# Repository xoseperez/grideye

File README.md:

# GridEye Camera

This is a 8x8 pixels IR camera based on the **Panasonic AMG88XX GridEye** sensors.
It uses a **WS2812 8x8 matrix** as camera display, an **128x32 uOLED display** for data and
a **Moteino** board with an ATMega328P microcontroller as controller.
It is powered by a **LiPo battery** connected to a **TP4056 based LiPO charger**.
There is also a **Pololu Adjustable Boost Regulator 2.5-9.5V** to power the LED matrix.

The AMG8833 is an 8x8 IR sensor by Panasonic with an I2C interface that reports concact-less temperature values from -20 to 80 celsius with a 2.5C accuracy and 0.25C resolution. It has a field view of ~60º and a max detection distance of 5 meters.

This is part of my "Slices" project, basically a sliced laser cut series of enclosures to house electronic projects.

## Hardware

### The electronics

The project relies on different discreet modules wired together. All the components (or compatible alternatives) are widely available. Only the AMG88XX board is custom made. Check the "amg8833" fordel in this repo for the Eagle files of the board.

All the dotted black lines in the drawing are connected together.

### The housing

The housing has been created using OpenSCAD and inspired by Pimoroni  PiBow enclosures for the RaspBerry Pi. I've been using this same technique lately on different project and I call them all under a common name: "Project Slices".

The enclosure is based on layers or "slices" of different materials.

* Transparent acrylic front-face
* Black cardboard mask
* White paper diffusor
* 4mm MDF grid that houses each LED in its own cubicle
* 2.5mm MDF cast for the LED matrix PCB
* 2.5mm MDF as support for the matrix PCB and uOLED board
* several (5) 4mm MDF hollow layers to house the electronics
* 2.5mm MDF as support for the AMG88XX board
* 4mm MDF hollow layers to house the AMG88XX board
* 2.5mm MDF as a back pane with a hole for the IR sensor

## Firmware

The project is ready to be build using [PlatformIO](http://www.platformio.org).
Please refer to their web page for instructions on how to install the builder.
Once installed:

```bash
> cd code
> platformio run
> platformio run --target upload
```

Library dependencies are automatically managed via PlatformIO Library Manager.

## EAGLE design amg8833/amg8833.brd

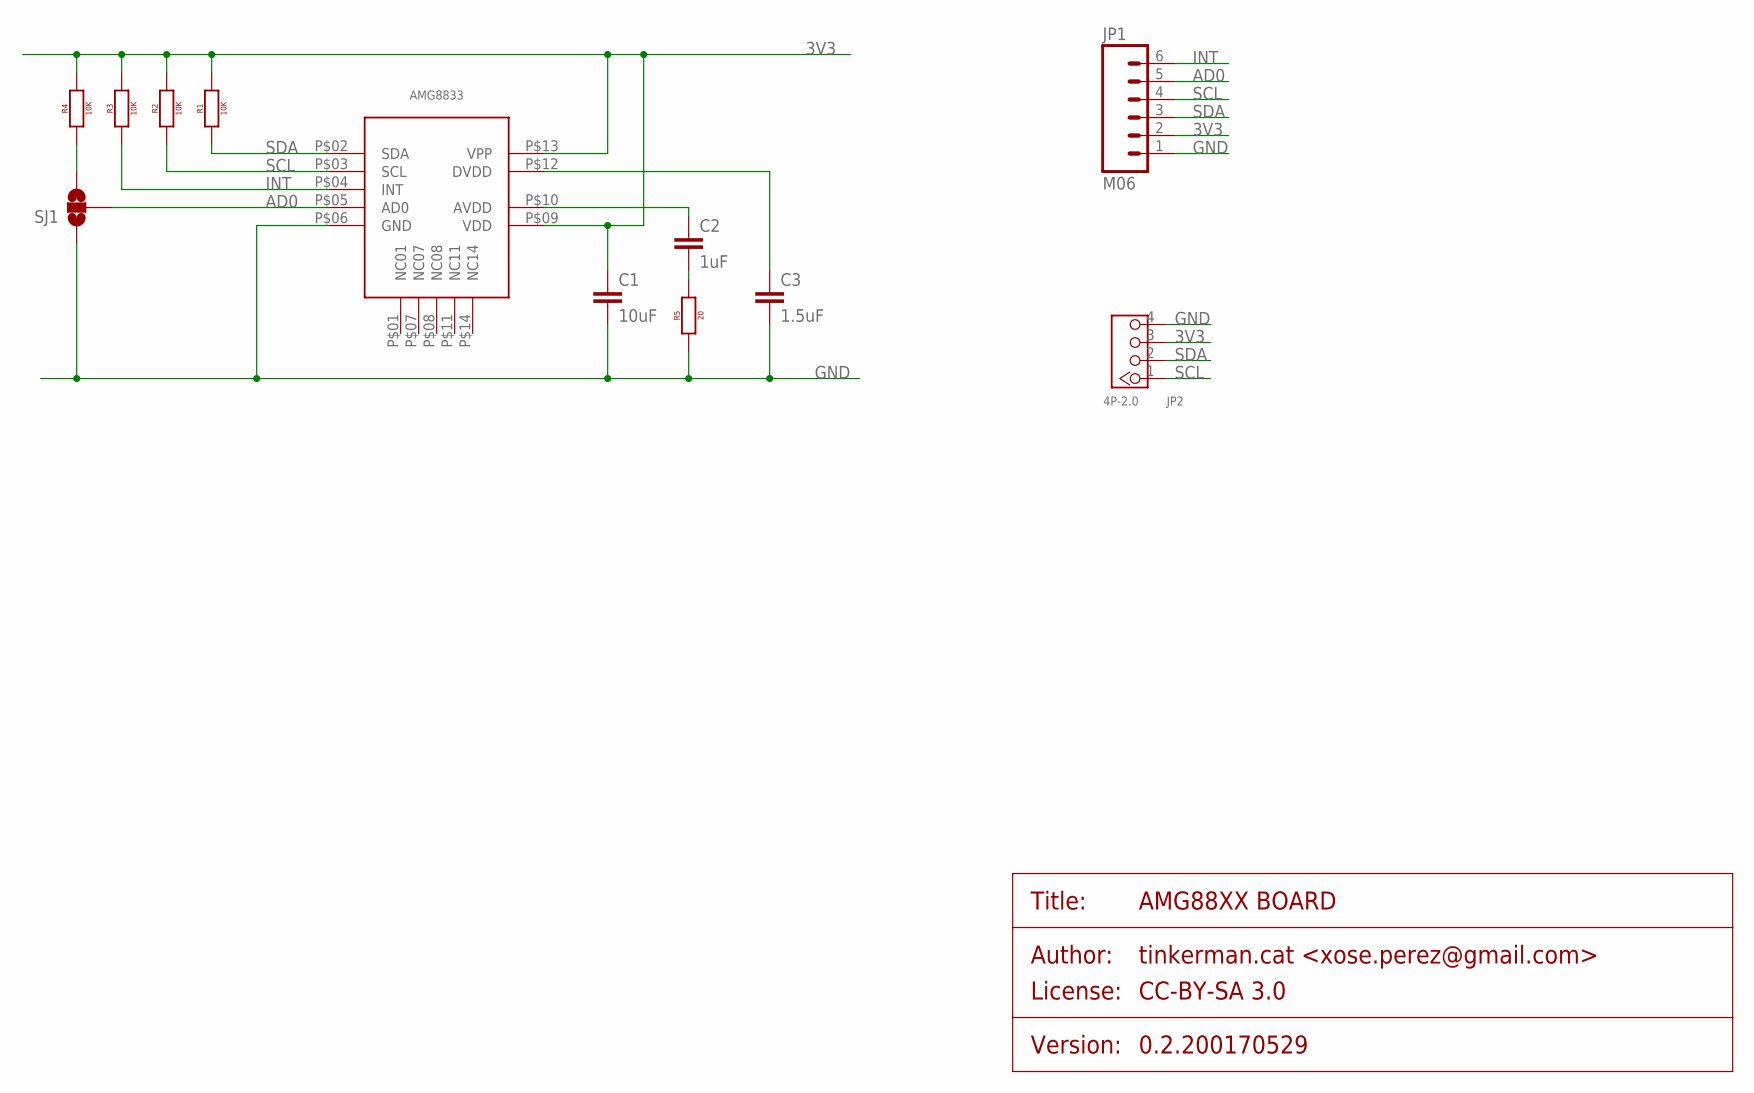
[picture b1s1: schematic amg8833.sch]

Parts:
AMG8833: AMG88XX
C1: 10uF; 0805
C2: 1uF; 0805
C3: 1.5uF; 0805
JP1: M06; 1X06_NO_SILK
JP2: 4P-2.0; HW4-2.0
R1, R2, R3, R4: 10K; 0805
R5: 20; 0805
SJ1: SOLDERJUMPER_2WAYS; SJ_3

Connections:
3V3: AMG8833.P$09 (VDD), AMG8833.P$13 (VPP), C1.1, JP1.2, JP2.3, R1.2, R2.2, R3.2, R4.2
AD0: AMG8833.P$05 (AD0), JP1.5, SJ1.2
GND: AMG8833.P$06 (GND), C1.2, C3.2, JP1.1, JP2.4, R5.1, SJ1.1
INT: AMG8833.P$04 (INT), JP1.6, R3.1
unnamed: R4.1, SJ1.3
unnamed: C2.2, R5.2
unnamed: AMG8833.P$12 (DVDD), C3.1
unnamed: AMG8833.P$10 (AVDD), C2.1
SCL: AMG8833.P$03 (SCL), JP1.4, JP2.1, R2.1
SDA: AMG8833.P$02 (SDA), JP1.3, JP2.2, R1.1

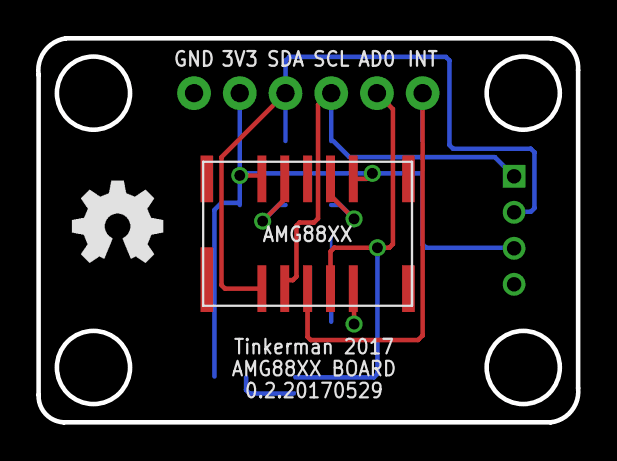
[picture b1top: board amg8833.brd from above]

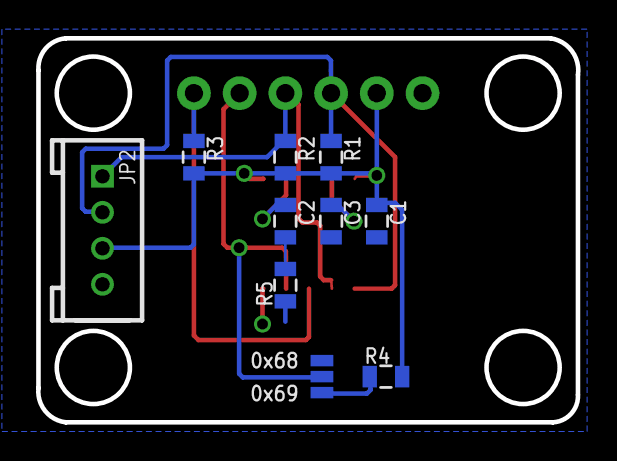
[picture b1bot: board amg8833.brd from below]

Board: 2 copper layers, 30.0 x 21.3 mm, 12 parts (10 on the bottom side), 10 nets.

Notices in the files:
amg8833/amg8833.sch:
PROJECT_LICENSE: CC-BY-SA 3.0
